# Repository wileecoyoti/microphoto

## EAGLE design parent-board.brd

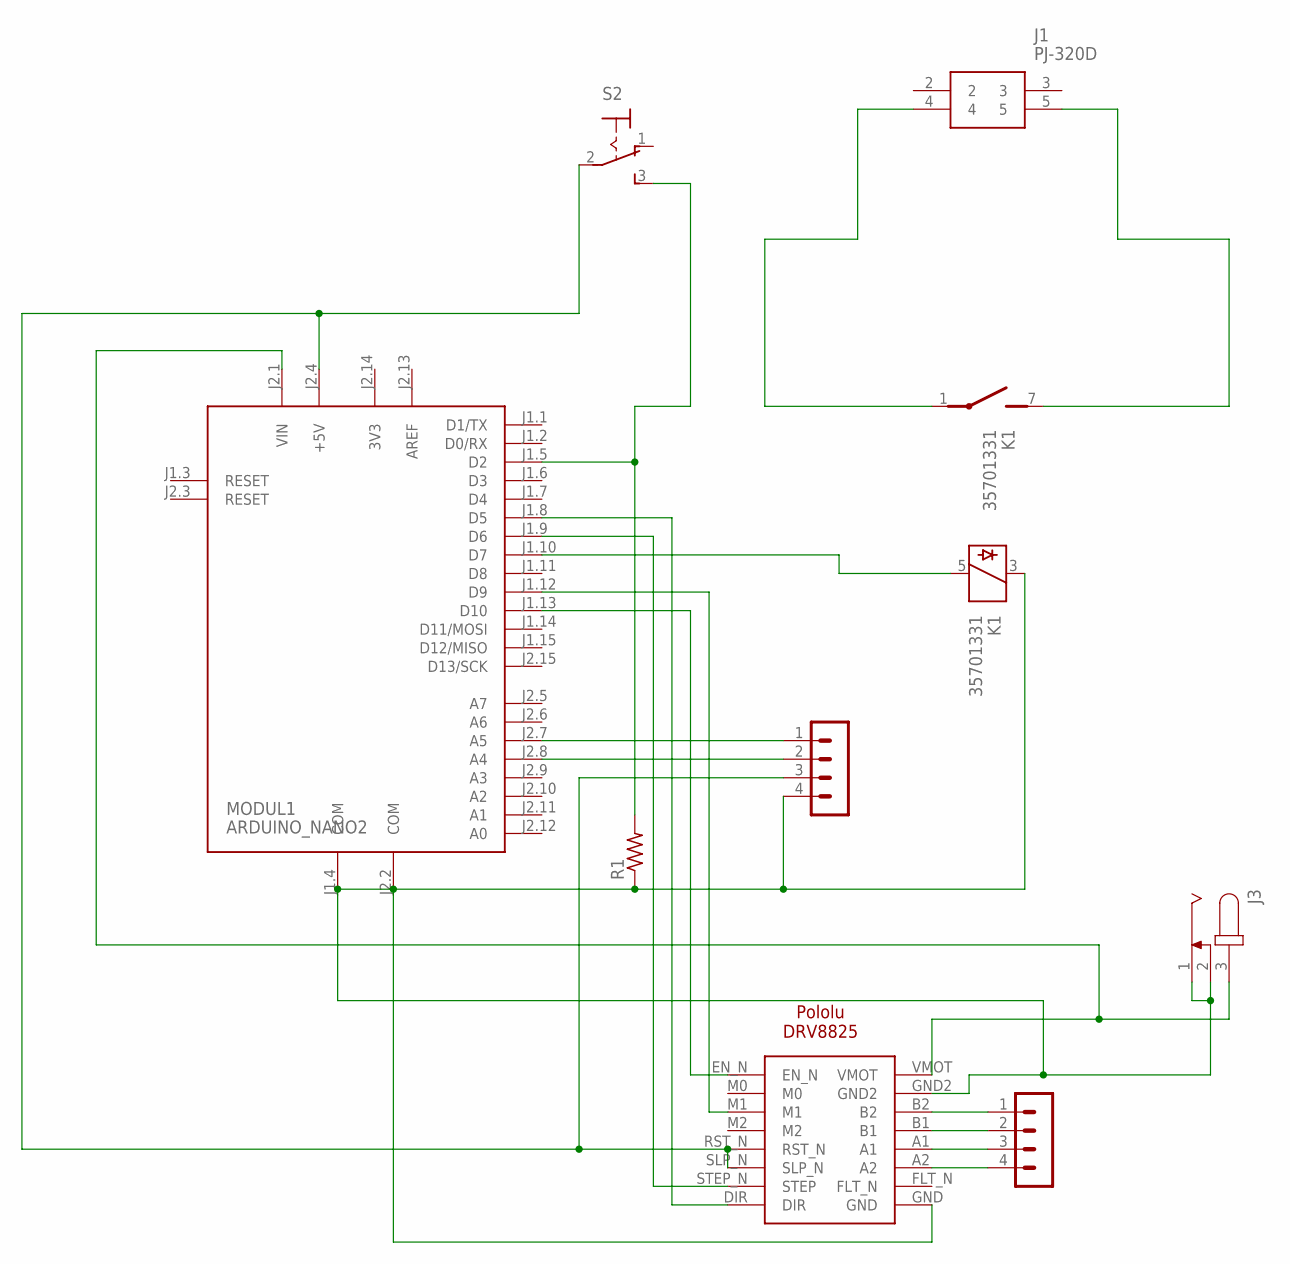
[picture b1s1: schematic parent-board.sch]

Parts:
J1: PJ-320D; PJ320D
J2, J4: MA04-1
J3: JACK-PLUG0; SPC4077
K1: 35701331; REED
MODUL1: ARDUINO_NANO2
R1: R-US_M1206; M1206
S2: 320-916
U$1: POLOLU-DRV8825

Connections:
3V3: MODUL1.J2.14 (3V3)
AREF: MODUL1.J2.13 (AREF)
unnamed: J1.4, K1.1
unnamed: J1.5, K1.7 (S)
unnamed: K1.5, MODUL1.J1.10 (D7)
unnamed: J2.3, U$1.A1
unnamed: J2.2, U$1.B1
unnamed: MODUL1.J1.5 (D2), R1.2, S2.3 (S)
unnamed: MODUL1.J1.9 (D6), U$1.STEP_N (STEP)
unnamed: MODUL1.J1.8 (D5), U$1.DIR
unnamed: J2.1, U$1.B2
unnamed: J4.1, MODUL1.J2.7 (A5)
unnamed: J4.2, MODUL1.J2.8 (A4)
unnamed: J2.4, U$1.A2
unnamed: J3.3, MODUL1.J2.1 (VIN), U$1.VMOT
unnamed: J3.1, J3.2, J4.4, K1.3, MODUL1.J1.4 (COM), MODUL1.J2.2 (COM), R1.1, U$1.GND, U$1.GND2
unnamed: J4.3, MODUL1.J2.4 (+5V), S2.2, U$1.RST_N, U$1.SLP_N
unnamed: MODUL1.J1.13 (D10), U$1.EN_N
unnamed: MODUL1.J1.12 (D9), U$1.M1

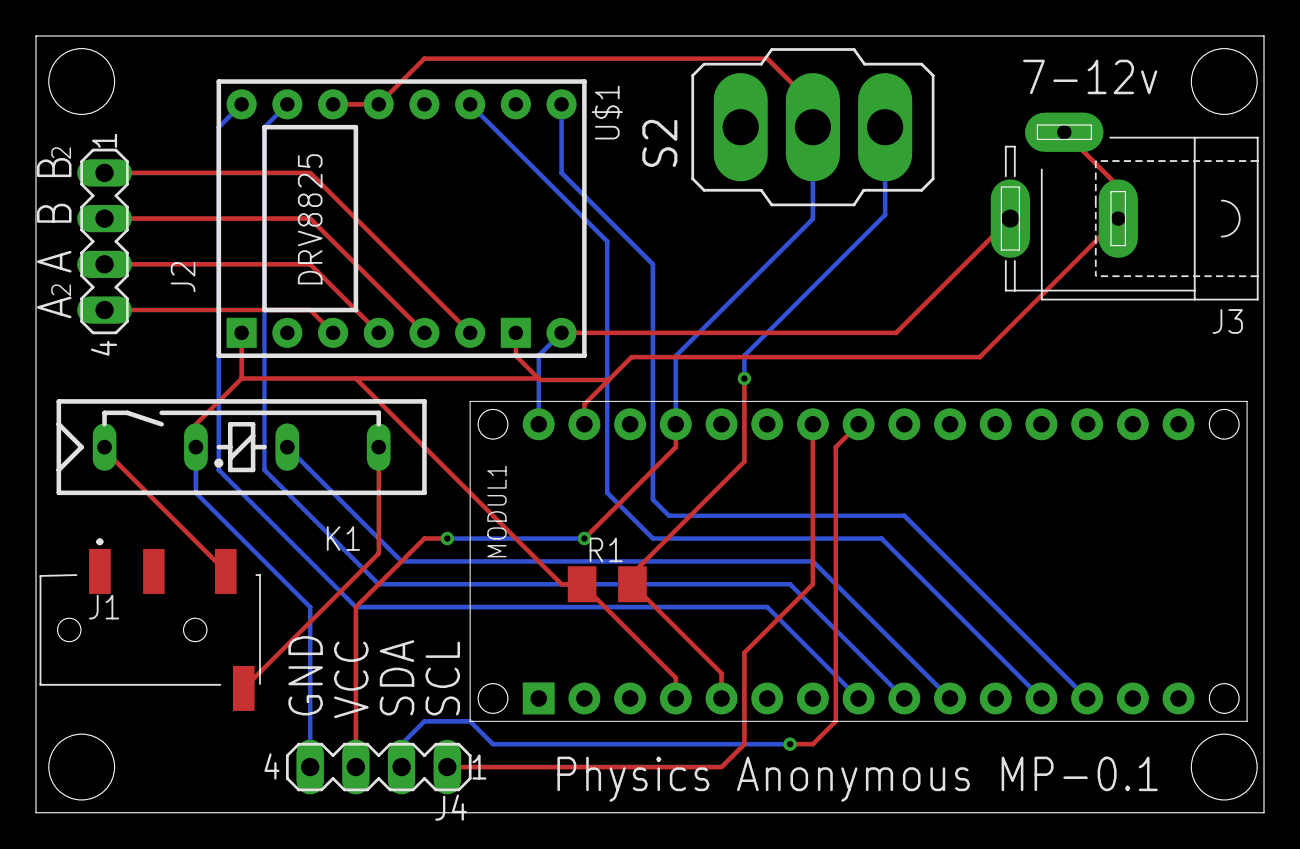
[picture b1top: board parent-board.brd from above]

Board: 2 copper layers, 68.2 x 43.2 mm, 9 parts (0 on the bottom side), 17 nets.
